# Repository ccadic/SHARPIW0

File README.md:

# SHARPIW0

The SHARPIW0 carrier board has been designed to hold both a Raspberry(R) PI ZERO 2W or W + 2.7"  (400x240) Sharp Memory Display. 
This display is capable of a fast refresh which allows the use of linux shells or display game images. 

The board also has 4 independently controlable LEDs you can switch on/off with classic GPIO commands (C++ or Python) 

The board also has 5 buttons you may also control via GPIO voltage detection (UP/Down voltage detection).  You can use this board for gaming.

You can get a fully made board here: https://www.tindie.com/products/electronictrik/sharpiw0-a-rpi-zero-27-sharp-memory-display/ 
It is also a good way to support opensource devices creators

If you need PCB only: https://www.tindie.com/products/electronictrik/sharpiw0-rpi0w-27-sharp-display-pcb-only/

**Extra GPIO available**
 
We added several extra GPIO, should you want to add an external UART extra board or a I2C board.  For the maker, we also added access to the display pins with the right bottom line of 2.54 mm header pinout (SCK to GND). If you want, you can drive the LCD without the Raspberry PI ZERO , and replace it with a classic microcontroller. In the same idea, you have B1 to B5 buttons signals available on pins.

**Installation**
If the board and display come separate, please connect the display's ribbon to the white connector, ribbon contacts facing the board surface. 
Plug the Raspberry PI ZERO like show on the diagram below.

**Software setup**
The Buttons and LEDs are controleable using classic python scripts. 
For the display, you have to install 2 libraries/code and compile them

1° ONE BITE DISPLAY LIB:  https://github.com/bitbank2/OneBitDisplay
Install with git clone https://github.com/bitbank2/OneBitDisplay
Go to /linux/Sharp_LCD directory and type make. 

2° ARMBIANIO LIB: https://github.com/bitbank2/ArmbianIO
Install the lib with git clone https://github.com/bitbank2/ArmbianIO
and make

Go back to Go to /linux/Sharp_LCD directory and  run the compiled executable ./sharp_lcd

Have fun !
Dr CADIC Philippe

Special credits to : Larry Bank for hi precious help and support in this project. 
@fast_code_r_us

Link to new LCD if an accident occurs
Link to SHARP Display: https://fr.aliexpress.com/item/4000674316500.html

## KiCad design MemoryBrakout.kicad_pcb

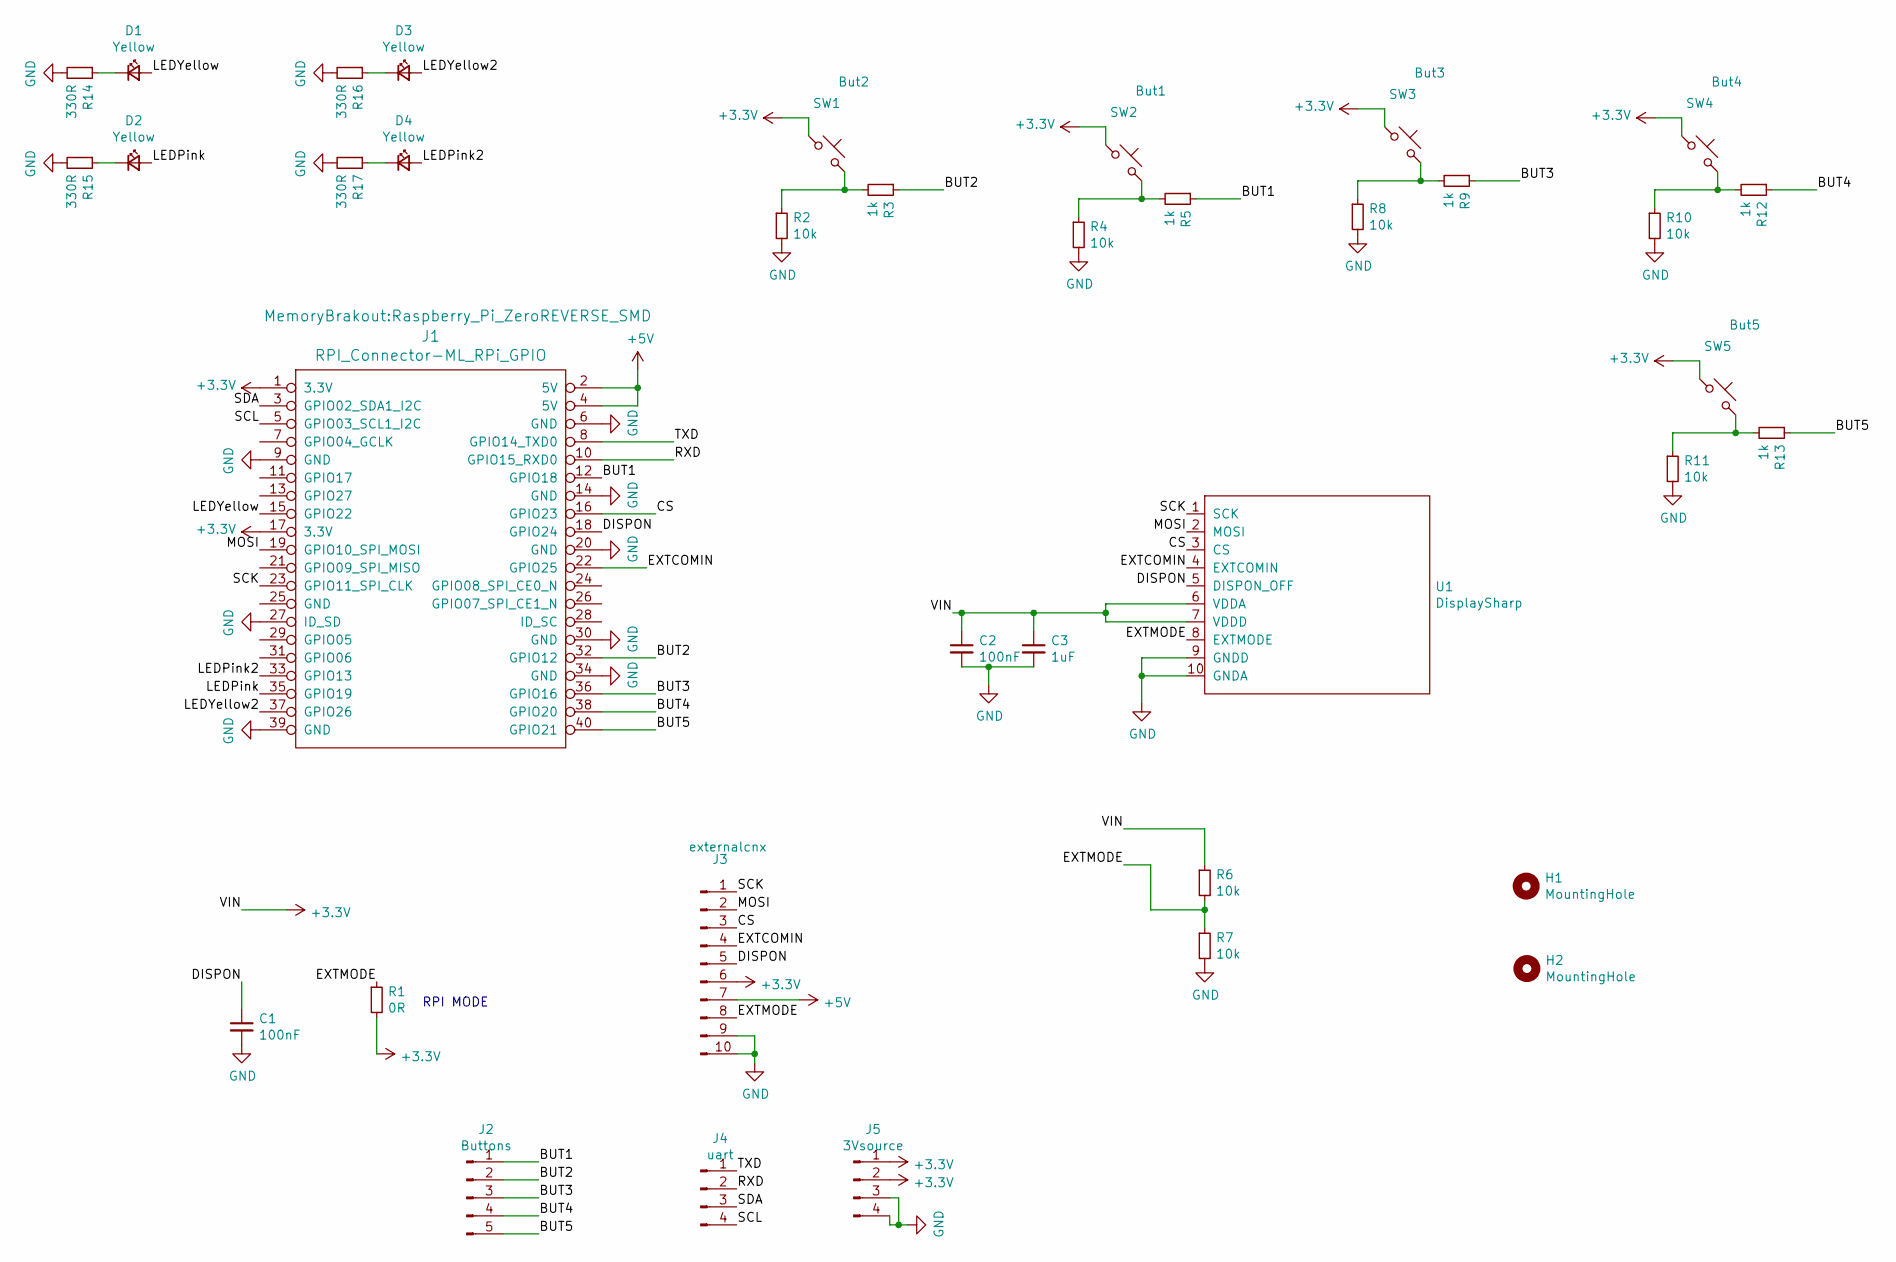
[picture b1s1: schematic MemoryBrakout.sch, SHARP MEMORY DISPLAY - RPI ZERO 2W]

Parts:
C1, C2: 100nF; C_0603_1608Metric_Pad1.08x0.95mm_HandSolder
C3: 1uF; C_0603_1608Metric_Pad1.08x0.95mm_HandSolder
D1, D2, D3, D4: Yellow; LED_0603_1608Metric_Castellated
H1, H2: MountingHole; MountingHole_2.5mm
J1: RPI_Connector-ML_RPi_GPIO; Raspberry_Pi_ZeroREVERSE_SMD
J2: Buttons; PinHeader_1x05_P2.54mm_Vertical
J3: externalcnx; PinHeader_1x10_P2.54mm_Vertical
J4: uart; PinHeader_1x04_P2.54mm_Vertical
J5: 3Vsource; PinHeader_1x04_P2.54mm_Vertical
R1: 0R; R_0603_1608Metric_Pad0.98x0.95mm_HandSolder
R2, R4, R6, R7, R8, R10, R11: 10k; R_0603_1608Metric_Pad0.98x0.95mm_HandSolder
R3, R5, R9, R12, R13: 1k; R_0603_1608Metric_Pad0.98x0.95mm_HandSolder
R14, R15, R16, R17: 330R; R_0603_1608Metric_Pad0.98x0.95mm_HandSolder
SW1: But2; SW_TP1003
SW2: But1; SW_TP1003
SW3: But3; SW_TP1003
SW4: But4; SW_TP1003
SW5: But5; SW_TP1003
U1: DisplaySharp; SHARP27LCD

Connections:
+3V3: C2.1, C3.1, J1.1 (3.3V), J1.17 (3.3V), J3.6, J5.1, J5.2, R1.2, R6.1, SW1.1, SW2.1, SW3.1, SW4.1, SW5.1, U1.6 (VDDA), U1.7 (VDDD)
+5V: J1.2 (5V), J1.4 (5V), J3.7
/BUT1: J1.12 (GPIO18), J2.1, R5.1
/BUT2: J1.32 (GPIO12), J2.2, R3.1
/BUT3: J1.36 (GPIO16), J2.3, R9.1
/BUT4: J1.38 (GPIO20), J2.4, R12.1
/BUT5: J1.40 (GPIO21), J2.5, R13.1
/CS: J1.16 (GPIO23), J3.3, U1.3 (CS)
/DISPON: C1.1, J1.18 (GPIO24), J3.5, U1.5 (DISPON_OFF)
/EXTCOMIN: J1.22 (GPIO25), J3.4, U1.4 (EXTCOMIN)
/EXTMODE: J3.8, R1.1, R6.2, R7.1, U1.8 (EXTMODE)
/LEDPink: D2.2 (A), J1.35 (GPIO19)
/LEDPink2: D4.2 (A), J1.33 (GPIO13)
/LEDYellow: D1.2 (A), J1.15 (GPIO22)
/LEDYellow2: D3.2 (A), J1.37 (GPIO26)
/MOSI: J1.19 (GPIO10_SPI_MOSI), J3.2, U1.2 (MOSI)
/RXD: J1.10 (GPIO15_RXD0), J4.2
/SCK: J1.23 (GPIO11_SPI_CLK), J3.1, U1.1 (SCK)
/SCL: J1.5 (GPIO03_SCL1_I2C), J4.4
/SDA: J1.3 (GPIO02_SDA1_I2C), J4.3
/TXD: J1.8 (GPIO14_TXD0), J4.1
GND: C1.2, C2.2, C3.2, J1.6 (GND), J1.9 (GND), J1.14 (GND), J1.20 (GND), J1.27 (ID_SD), J1.30 (GND), J1.34 (GND), J1.39 (GND), J3.9, J3.10, J5.3, J5.4, R2.2, R4.2, R7.2, R8.2, R10.2, R11.2, R14.2, R15.2, R16.2, R17.2, U1.9 (GNDD), U1.10 (GNDA)
unnamed: D1.1 (K), R14.1
unnamed: D2.1 (K), R15.1
unnamed: D3.1 (K), R16.1
unnamed: D4.1 (K), R17.1
unnamed: R2.1, R3.2, SW1.2
unnamed: R4.1, R5.2, SW2.2
unnamed: R8.1, R9.2, SW3.2
unnamed: R10.1, R12.2, SW4.2
unnamed: R11.1, R13.2, SW5.2

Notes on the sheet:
RPI MODE

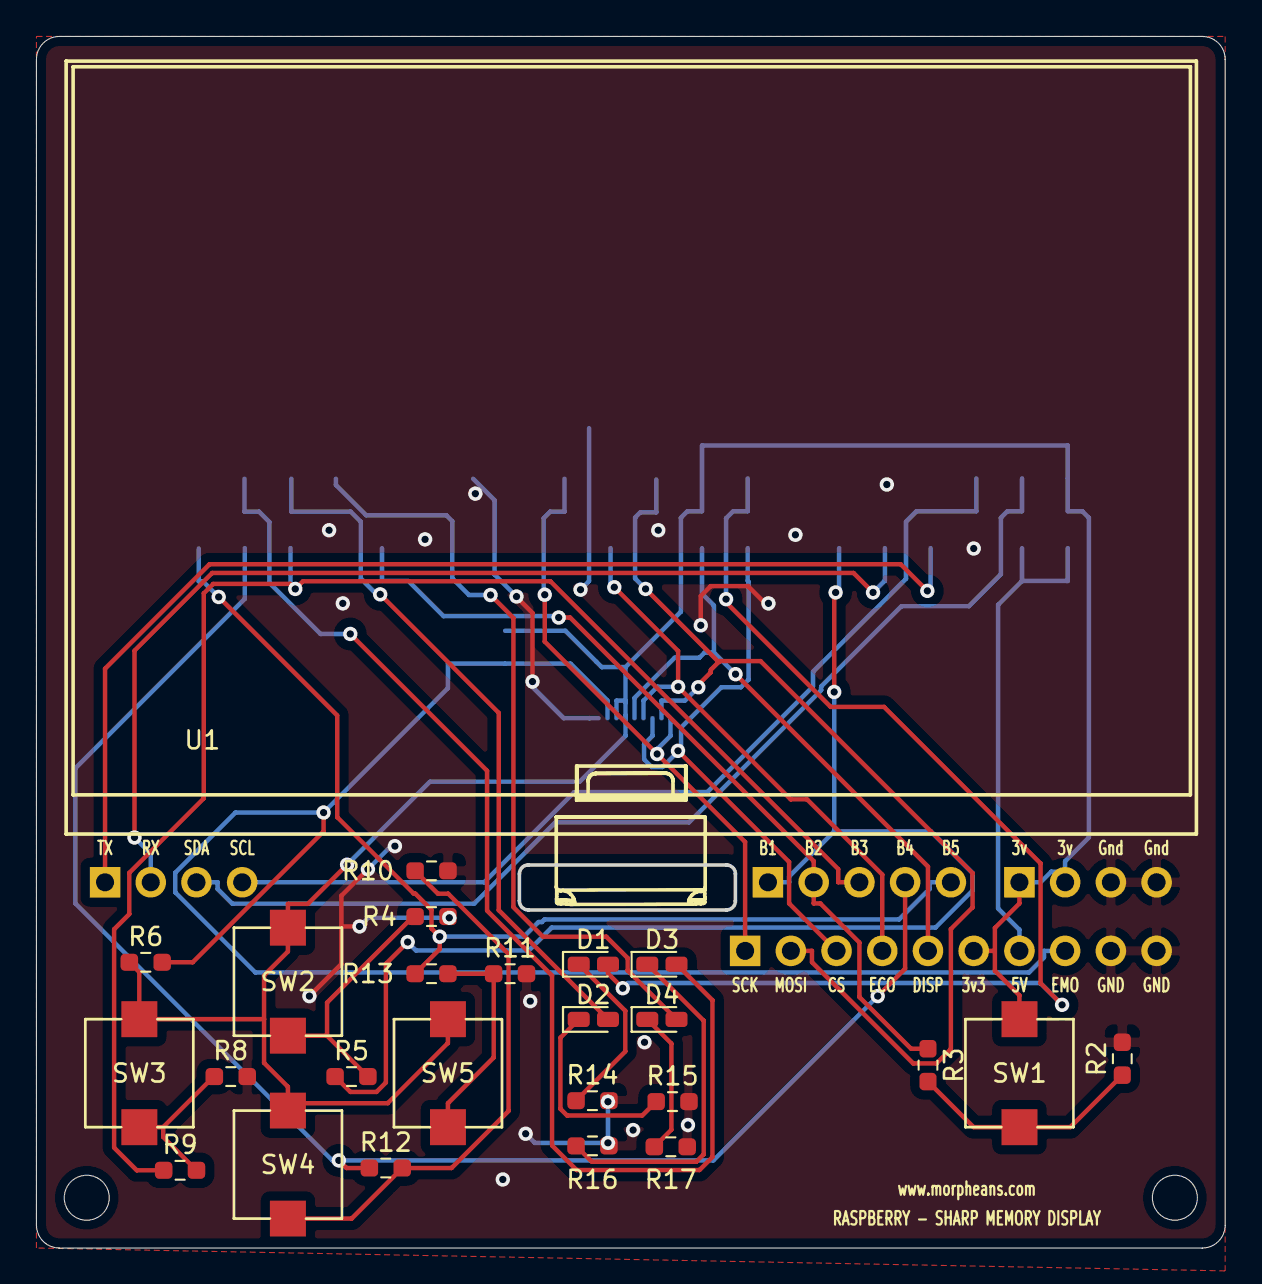
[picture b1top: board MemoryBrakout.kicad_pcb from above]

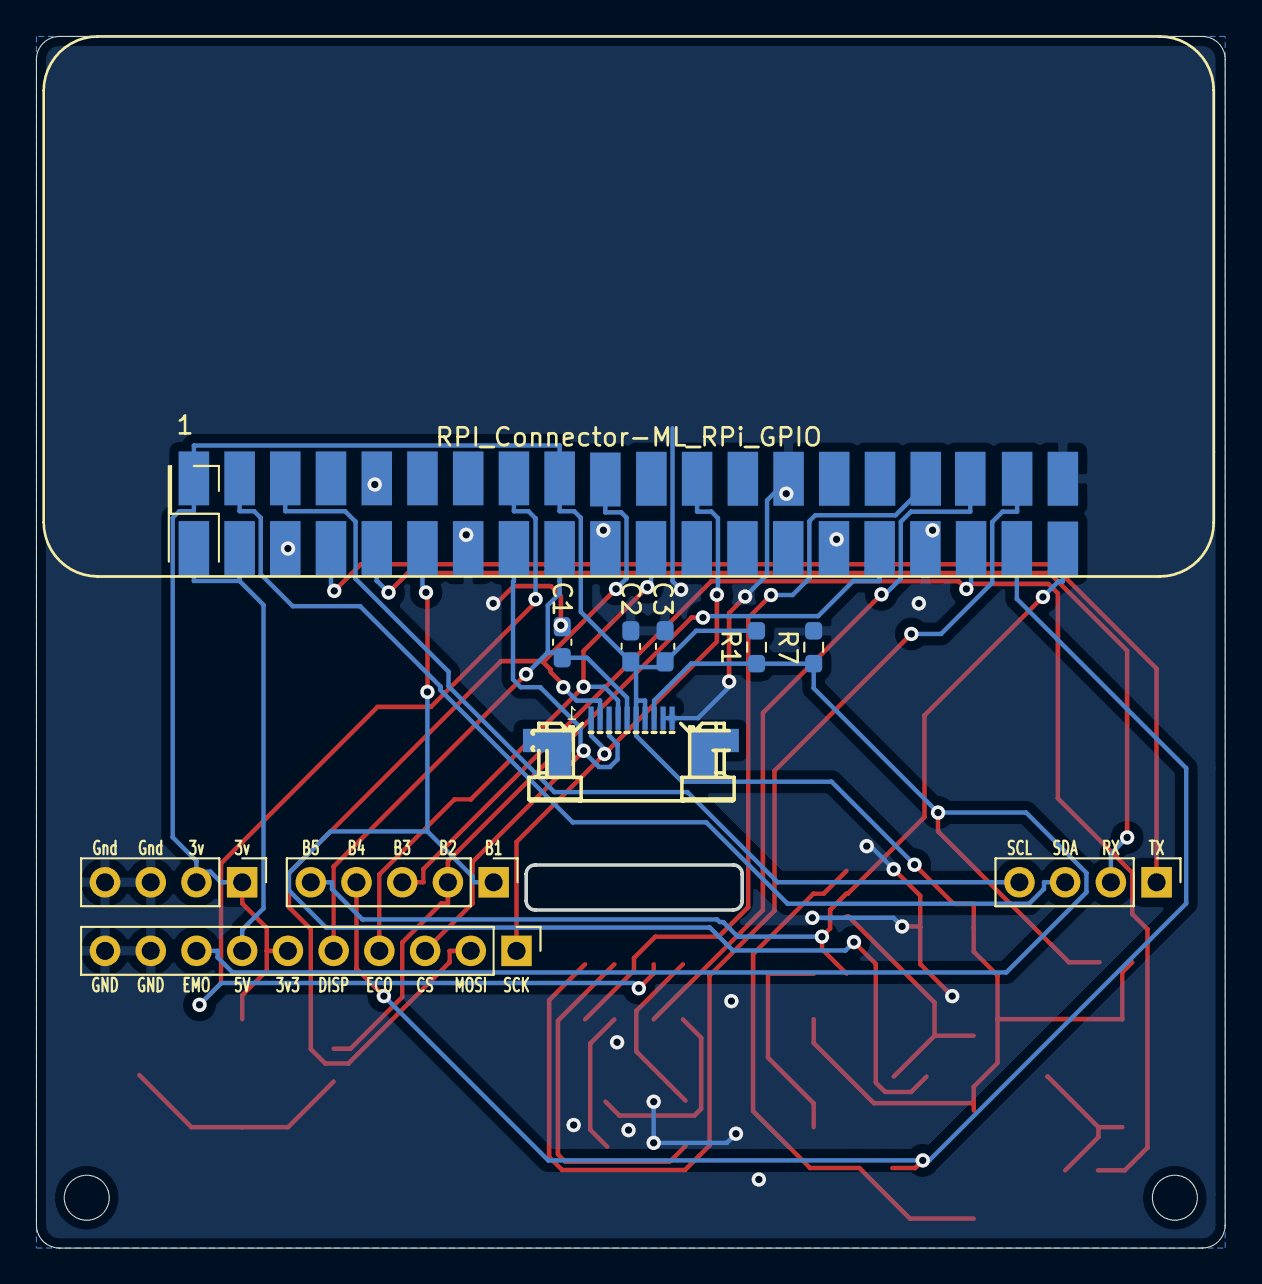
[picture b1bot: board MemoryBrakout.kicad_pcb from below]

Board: 2 copper layers, 65.9 x 67.2 mm, 37 parts (10 on the bottom side), 31 nets.
